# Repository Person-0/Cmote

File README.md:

# **Cmote**

A USB-C IR transmitter for controlling devices like ACs, TVs for when you're too lazy to find the remote and your smartphone does not have a built-in IR blaster. Built-in to a devboard powered by the Attiny1616 MCU.

# PCB
> View PCB Directory: [/PCB](./PCB)

Schematics:

PCB:

Preview PCB 3D View:

Steps to open the schematics and PCB files in KiCAD:
- Open KiCAD
- Click **File** (top left) >> **Open Project**
- Navigate to this repository's saved destination,
- Open **/PCB/Cmote** directory
- Select the file `Cmote.kicad_pro`

This will open the schematics and PCB in KiCAD for easier viewing!

# Firmware
> View firmware directory: [/firmware](./firmware/)

> Note that firmware is Work In Progress. Until I physically receive the board I have no way of knowing whether this works or not so current it is just basic stuff.

The current firmware will send a power command at the start, listen to all the IR signals and print them to the serial on USB-C port of the board:

```cpp
bool sentPwrCmd = false;

void setup() {
	Serial.begin(115200); // serial is on usb-c
	IrSender.begin(IR_TX_PIN);
	IrReceiver.begin(IR_RX_PIN, ENABLE_LED_FEEDBACK); 
}

void loop() {

	if (!sentPwrCmd) {
		uint16_t address = 0x00; // standard device address
		uint8_t command = 0x45;  // standard power command
		IrSender.sendNEC(address, command, 0);
		sentPwrCmd = true;
		Serial.println("=== power command was sent!! ===");
	}

	if (IrReceiver.decode()) {
		Serial.println("-------------------------");
		Serial.println("\tbegin decode():");
        Serial.print("Protocol: ");
        Serial.println(getProtocolString(IrReceiver.decodedIRData.protocol));
        Serial.print("Command (Hex): 0x");
        Serial.println(IrReceiver.decodedIRData.command, HEX);
        Serial.print("Address (Hex): 0x");
        Serial.println(IrReceiver.decodedIRData.address, HEX);
        Serial.println("-------------------------\n");
        IrReceiver.resume(); 
    }

}
```

**IrReceiver and IrSender is from the [IRremote](https://registry.platformio.org/libraries/z3t0/IRremote) library.**

As for flashing the firmware onto the board, it requires a specialized UPDI programmer. However, I will be using another devboard to program this using **[pyupdi](https://github.com/mraardvark/pyupdi/)**. This guide will be updated after I test it myself to confirm what works and what does not.

# CAD
> View CAD Directory: [/CAD](./CAD)

While this is technically a devboard and has no requirement for a case, I still made one using Fusion360.

It looks like this:

> USB-C plug is invisible as no model was available for it from the manufacturer so I made sure to give enough space by measuring the silkscreen dimensions on the PCB and using it as the reference.

The lid will friction fit into the case using the side extrusions.

It has rectangular cuts for headers so the devboard can be freely used without taking off the lid again and again.

**For 3d printing, files [Cmote_body.step](./CAD/Cmote_body.step) and [Cmote_lid.step](./CAD/Cmote_lid.step) need to be printed as different bodies.**

## Ordering Parts

I will be using JLCPCB to order my PCB as for my location it is the cheapest option (if using PCB Assembly service).

Please checkout the [JLC_Order](./PCB/JLC_Order/) directory for bom, cpl and gerber files.

The grand total for this project comes out to be at `42.24 USD`

- This is when I have used basic parts when possible and only 2 PCBA with 5 PCB (moq)

[View BOM](./bom.csv) <br>
[View PCBA BOM](./PCB/JLC_Order/pcb_bom.csv) <br>

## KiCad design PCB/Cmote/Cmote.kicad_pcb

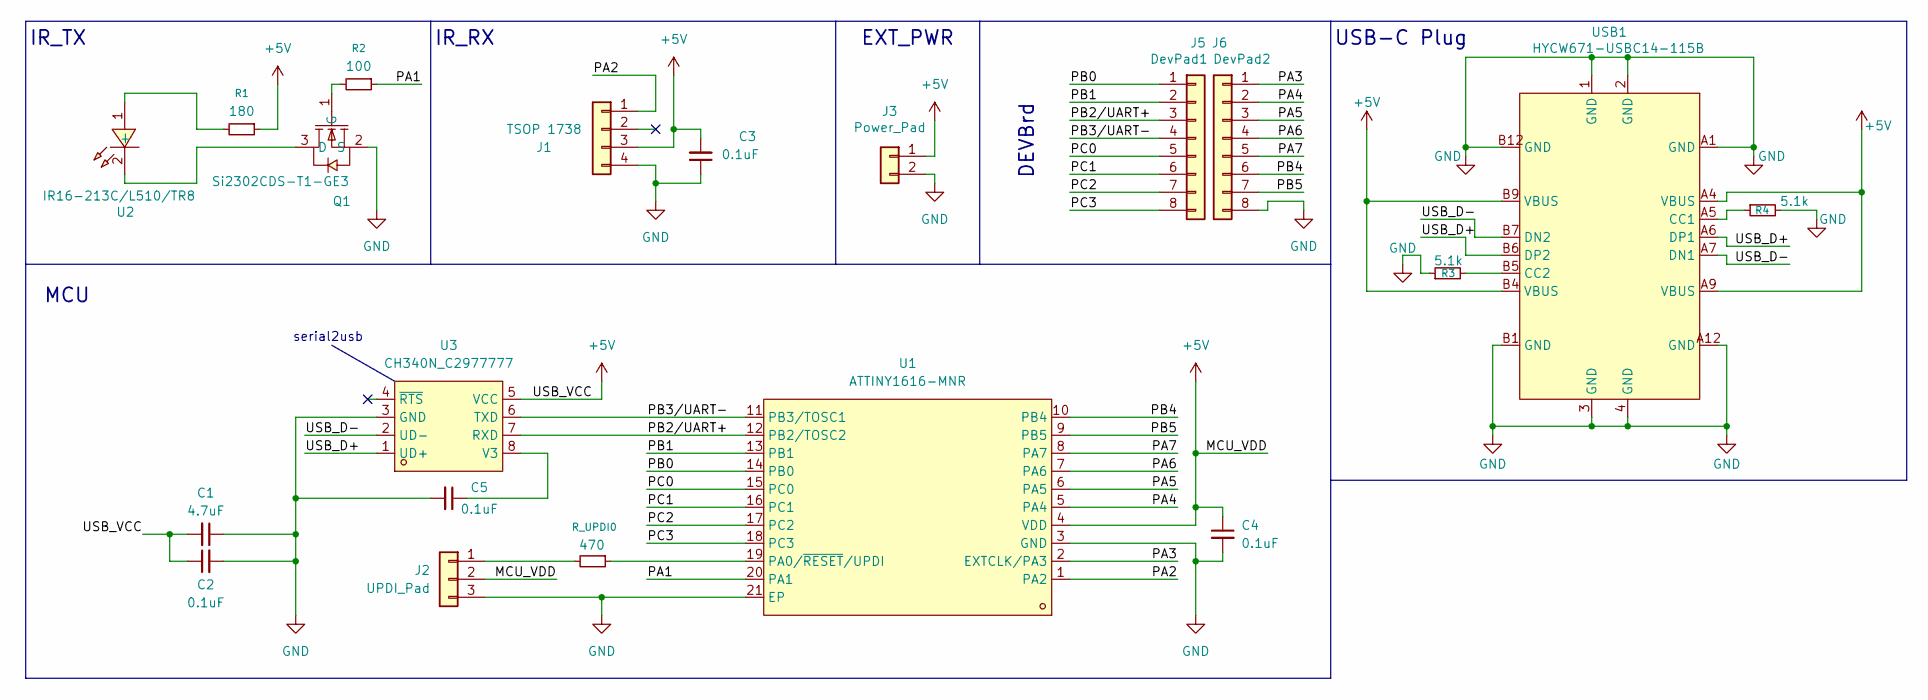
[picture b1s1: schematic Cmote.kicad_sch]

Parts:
C1: 4.7uF; C0402; MPN CL10A475KO8NNNC; LCSC Part C19666
C2, C3, C4, C5: 0.1uF; C0402; MPN CL05B104KO5NNNC; LCSC Part C1525
J1: TSOP 1738; PinHeader_1x04_P2.54mm_Vertical
J2: UPDI_Pad; PinHeader_1x03_P2.54mm_Vertical
J3: Power_Pad; PinHeader_1x02_P2.54mm_Vertical
J5: DevPad1; PinHeader_1x08_P2.54mm_Vertical
J6: DevPad2; PinHeader_1x08_P2.54mm_Vertical
Q1: Si2302CDS-T1-GE3; SOT-23_L2.9-W1.3-P1.90-LS2.4-BR; MPN Si2302CDS-T1-GE3; LCSC Part C10488
R1: 180; R0402; MPN RC0402JR-07180RL; LCSC Part C137913
R2: 100; R0402; MPN 0402WGF1000TCE; LCSC Part C25076
R3, R4: 5.1k; R0402; MPN 0402WGF5101TCE; LCSC Part C25905
R_UPDI0: 470; R0402; MPN 0402WGF4700TCE; LCSC Part C25117
U1: ATTINY1616-MNR; QFN-20_L3.0-W3.0-P0.40-BL-EP1.7; MPN ATTINY1616-MNR; LCSC Part C507118
U2: IR16-213C/L510/TR8; LED0402-FD_YELLOW; MPN IR16-213C/L510/TR8; LCSC Part C2943465
U3: CH340N_C2977777; SOP-8_L4.9-W3.9-P1.27-LS6.0-BL; MPN CH340N; LCSC Part C2977777
USB1: HYCW671-USBC14-115B; USB-SMD_HYCW671-USBC14-115B; MPN HYCW671-USBC14-115B; LCSC Part C53436581

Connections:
+5V: C1.2, C2.1, C3.2, C4.1, J1.3, J2.2, J3.1, R1.1, U1.4 (VDD), U3.5 (VCC), USB1.A4 (VBUS), USB1.A9 (VBUS), USB1.B4 (VBUS), USB1.B9 (VBUS)
/PA1: R2.1, U1.20 (PA1)
/PA2: J1.1, U1.1 (PA2)
/PA3: J6.1, U1.2 (EXTCLK/PA3)
/PA4: J6.2, U1.5 (PA4)
/PA5: J6.3, U1.6 (PA5)
/PA6: J6.4, U1.7 (PA6)
/PA7: J6.5, U1.8 (PA7)
/PB0: J5.1, U1.14 (PB0)
/PB1: J5.2, U1.13 (PB1)
/PB2/UART+: J5.3, U1.12 (PB2/TOSC2), U3.7 (RXD)
/PB3/UART-: J5.4, U1.11 (PB3/TOSC1), U3.6 (TXD)
/PB4: J6.6, U1.10 (PB4)
/PB5: J6.7, U1.9 (PB5)
/PC0: J5.5, U1.15 (PC0)
/PC1: J5.6, U1.16 (PC1)
/PC2: J5.7, U1.17 (PC2)
/PC3: J5.8, U1.18 (PC3)
/USB_D+: U3.1 (UD+), USB1.A6 (DP1), USB1.B6 (DP2)
/USB_D-: U3.2 (UD-), USB1.A7 (DN1), USB1.B7 (DN2)
GND: C1.1, C2.2, C3.1, C4.2, C5.2, J1.4, J2.3, J3.2, J6.8, Q1.2 (S), R3.1, R4.2, U1.3 (GND), U1.21 (EP), U3.3 (GND), USB1.1 (GND), USB1.2 (GND), USB1.3 (GND), USB1.4 (GND), USB1.A1 (GND), USB1.A12 (GND), USB1.B1 (GND), USB1.B12 (GND)
unnamed: J2.1, R_UPDI0.2
unnamed: Q1.3 (D), U2.2 (-)
unnamed: Q1.1 (G), R2.2
unnamed: R_UPDI0.1, U1.19 (PA0/~RESET/UPDI)
unnamed: R1.2, U2.1 (+)
unnamed: C5.1, U3.8 (V3)
unnamed: R4.1, USB1.A5 (CC1)
unnamed: R3.2, USB1.B5 (CC2)

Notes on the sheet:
EXT_PWR
IR_TX
serial2usb
USB-C Plug
MCU
DEVBrd
IR_RX

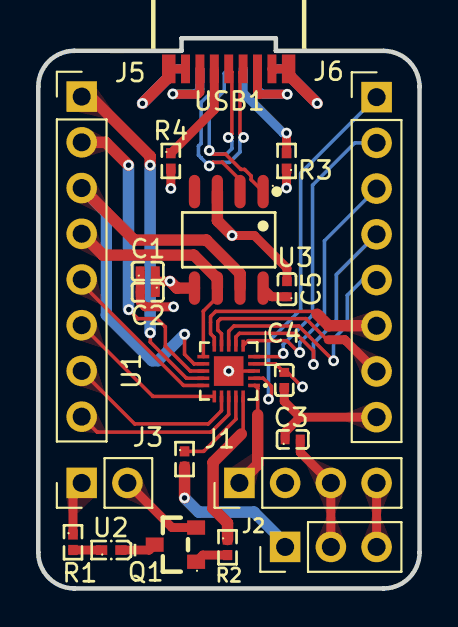
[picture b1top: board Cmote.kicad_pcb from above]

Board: 4 copper layers, 21.2 x 30.6 mm, 20 parts (0 on the bottom side), 29 nets.
